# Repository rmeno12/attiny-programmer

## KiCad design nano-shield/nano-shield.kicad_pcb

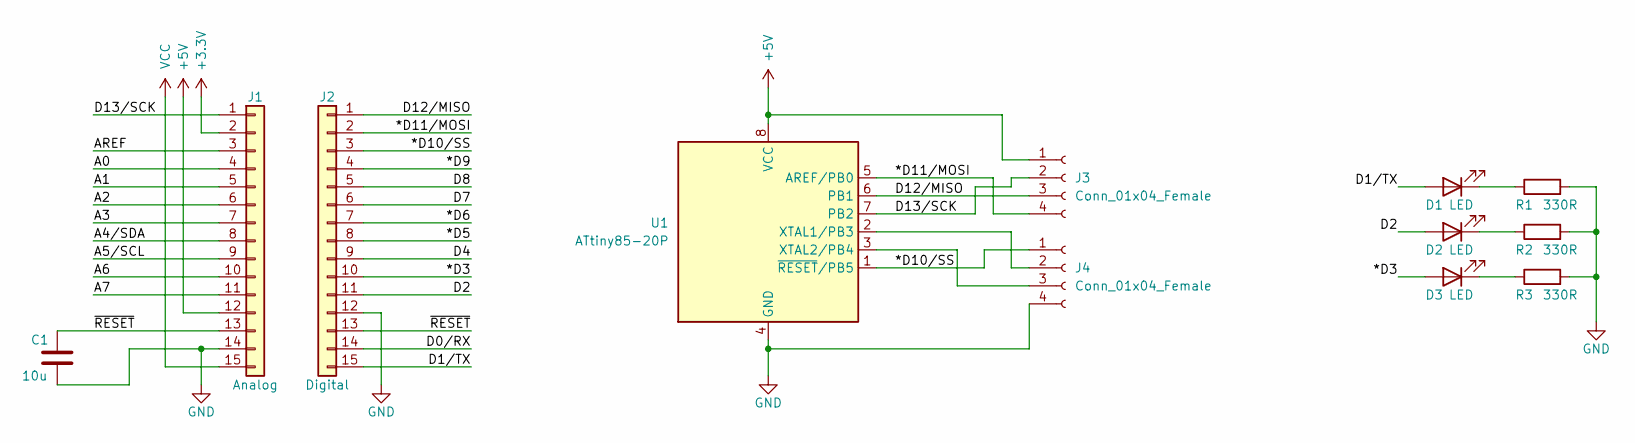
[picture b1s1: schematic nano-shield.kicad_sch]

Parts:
C1: 10u; C_0603_1608Metric
D1, D2, D3: LED; LED_0603_1608Metric
J1: Analog; PinSocket_1x15_P2.54mm_Vertical
J2: Digital; PinSocket_1x15_P2.54mm_Vertical
J3, J4: Conn_01x04_Female; PinSocket_1x04_P2.54mm_Vertical
R1, R2, R3: 330R; R_0603_1608Metric
U1: ATtiny85-20P; DIP-8_W7.62mm_Socket

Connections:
+3V3: J1.2
+5V: J1.12, J3.1, U1.8 (VCC)
/*D3: D3.2 (A), J2.10
/*D5: J2.8
/*D6: J2.7
/*D9: J2.4
/*D10/SS: J2.3, J4.1, U1.1 (~RESET/PB5)
/*D11/MOSI: J2.2, J3.4, U1.5 (AREF/PB0)
/A0: J1.4
/A1: J1.5
/A2: J1.6
/A3: J1.7
/A4/SDA: J1.8
/A5/SCL: J1.9
/A6: J1.10
/A7: J1.11
/AREF: J1.3
/D0/RX: J2.14
/D1/TX: D1.2 (A), J2.15
/D2: D2.2 (A), J2.11
/D4: J2.9
/D7: J2.6
/D8: J2.5
/D12/MISO: J2.1, J3.3, U1.6 (PB1)
/D13/SCK: J1.1, J3.2, U1.7 (PB2)
/~RESET: C1.1, J1.13, J2.13
GND: C1.2, J1.14, J2.12, J4.4, R1.2, R2.2, R3.2, U1.4 (GND)
unnamed: D1.1 (K), R1.1
unnamed: D2.1 (K), R2.1
unnamed: D3.1 (K), R3.1
unnamed: J4.2, U1.2 (XTAL1/PB3)
unnamed: J4.3, U1.3 (XTAL2/PB4)
VCC: J1.15

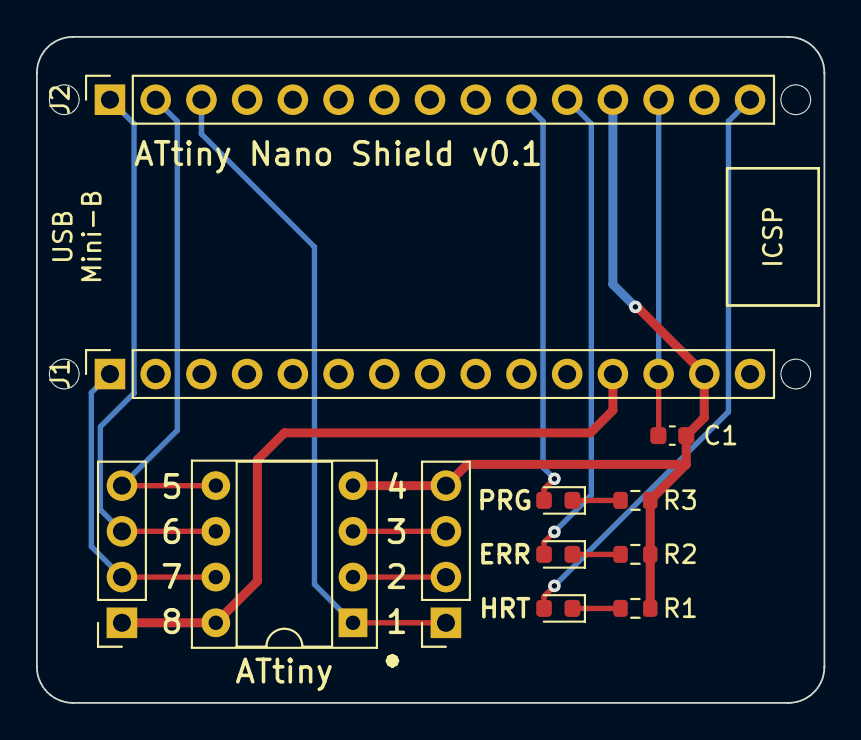
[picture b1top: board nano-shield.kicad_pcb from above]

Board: 2 copper layers, 43.8 x 37.0 mm, 16 parts (0 on the bottom side), 15 nets.

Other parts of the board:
MH1, MH2, MH3, MH4: MountingHole_65mil

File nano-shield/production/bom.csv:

Designator,Footprint,Quantity,Value,LCSC Part #
C1,C_0603_1608Metric,1,10u,
"D1, D2, D3",LED_0603_1608Metric,3,LED,
J1,PinSocket_1x15_P2.54mm_Vertical,1,Analog,
J2,PinSocket_1x15_P2.54mm_Vertical,1,Digital,
"J3, J4",PinSocket_1x04_P2.54mm_Vertical,2,Conn_01x04_Female,
"R1, R2, R3",R_0603_1608Metric,3,330R,
U1,DIP-8_W7.62mm_Socket,1,ATtiny85-20P,

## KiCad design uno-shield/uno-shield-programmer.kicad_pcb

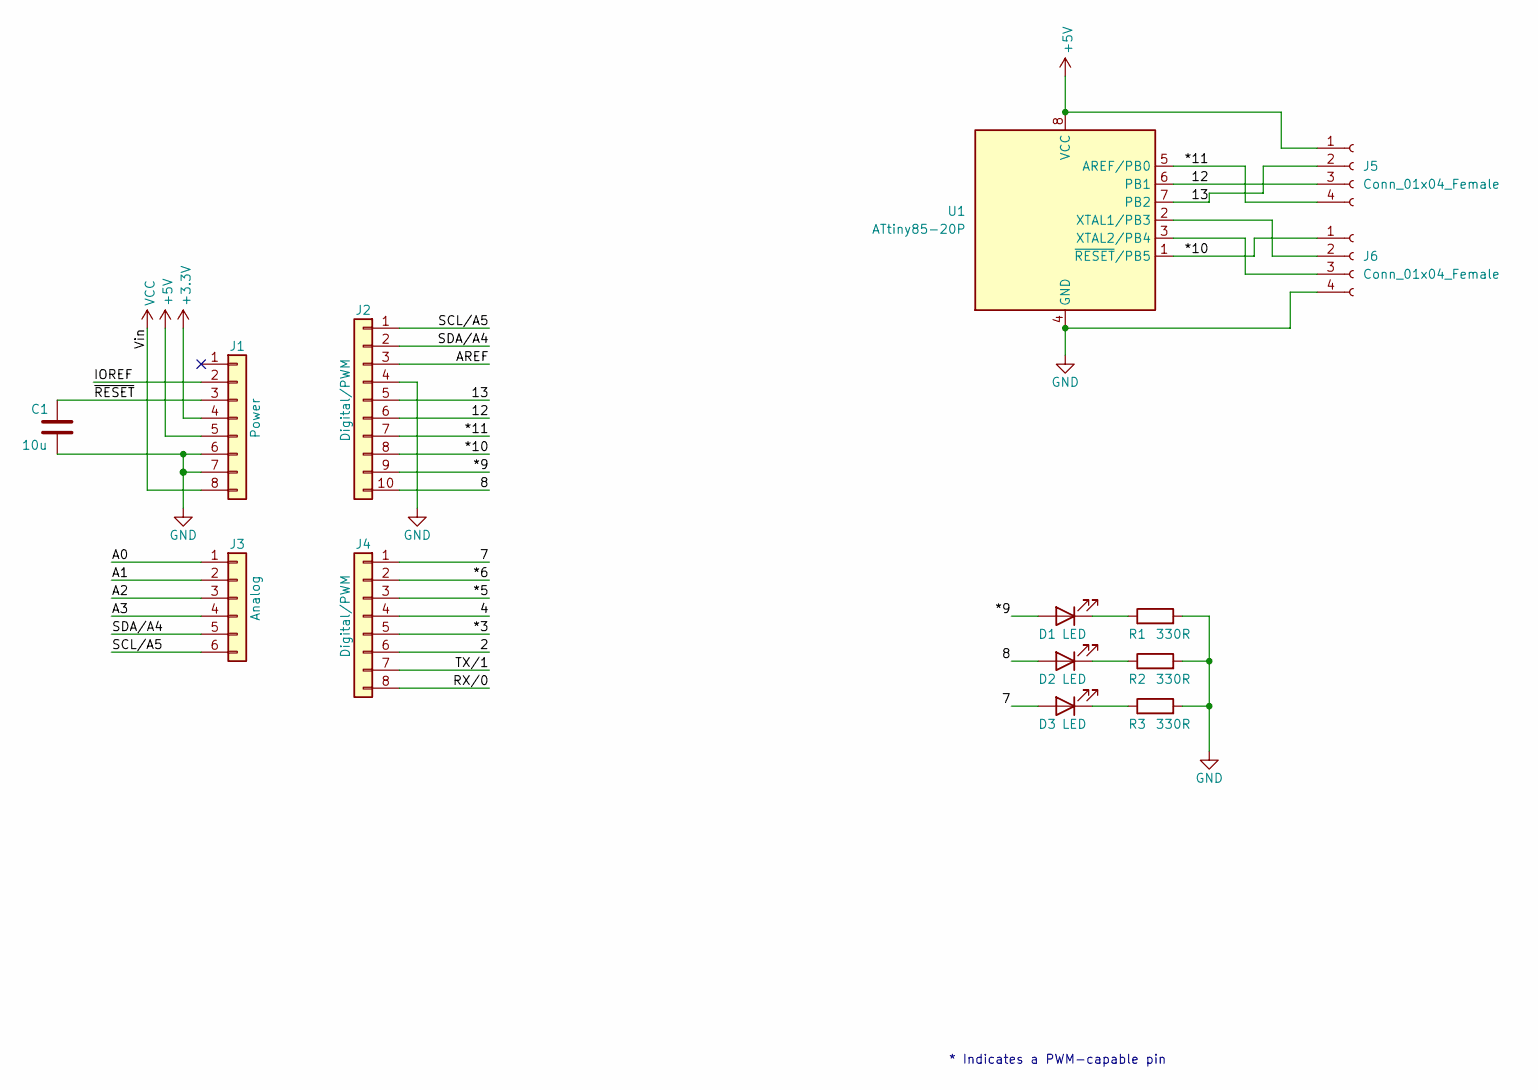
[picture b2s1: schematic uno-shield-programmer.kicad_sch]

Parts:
C1: 10u; C_0603_1608Metric
D1, D2, D3: LED; LED_0603_1608Metric
J1: Power; PinSocket_1x08_P2.54mm_Vertical
J2: Digital/PWM; PinSocket_1x10_P2.54mm_Vertical
J3: Analog; PinSocket_1x06_P2.54mm_Vertical
J4: Digital/PWM; PinSocket_1x08_P2.54mm_Vertical
J5, J6: Conn_01x04_Female; PinSocket_1x04_P2.54mm_Vertical
R1, R2, R3: 330R; R_0603_1608Metric
U1: ATtiny85-20P; DIP-8_W7.62mm_Socket

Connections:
+3V3: J1.4
+5V: J1.5, J5.1, U1.8 (VCC)
/2: J4.6
/4: J4.4
/7: D3.2 (A), J4.1
/8: D2.2 (A), J2.10
/12: J2.6, J5.3, U1.6 (PB1)
/13: J2.5, J5.2, U1.7 (PB2)
/*3: J4.5
/*5: J4.3
/*6: J4.2
/*9: D1.2 (A), J2.9
/*10: J2.8, J6.1, U1.1 (~RESET/PB5)
/*11: J2.7, J5.4, U1.5 (AREF/PB0)
/A0: J3.1
/A1: J3.2
/A2: J3.3
/A3: J3.4
/AREF: J2.3
/IOREF: J1.2
/RX/0: J4.8
/SCL/A5: J2.1, J3.6
/SDA/A4: J2.2, J3.5
/TX/1: J4.7
/~RESET: C1.1, J1.3
GND: C1.2, J1.6, J1.7, J2.4, J6.4, R1.2, R2.2, R3.2, U1.4 (GND)
unnamed: D1.1 (K), R1.1
unnamed: D2.1 (K), R2.1
unnamed: D3.1 (K), R3.1
unnamed: J6.2, U1.2 (XTAL1/PB3)
unnamed: J6.3, U1.3 (XTAL2/PB4)
VCC: J1.8

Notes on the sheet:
* Indicates a PWM-capable pin

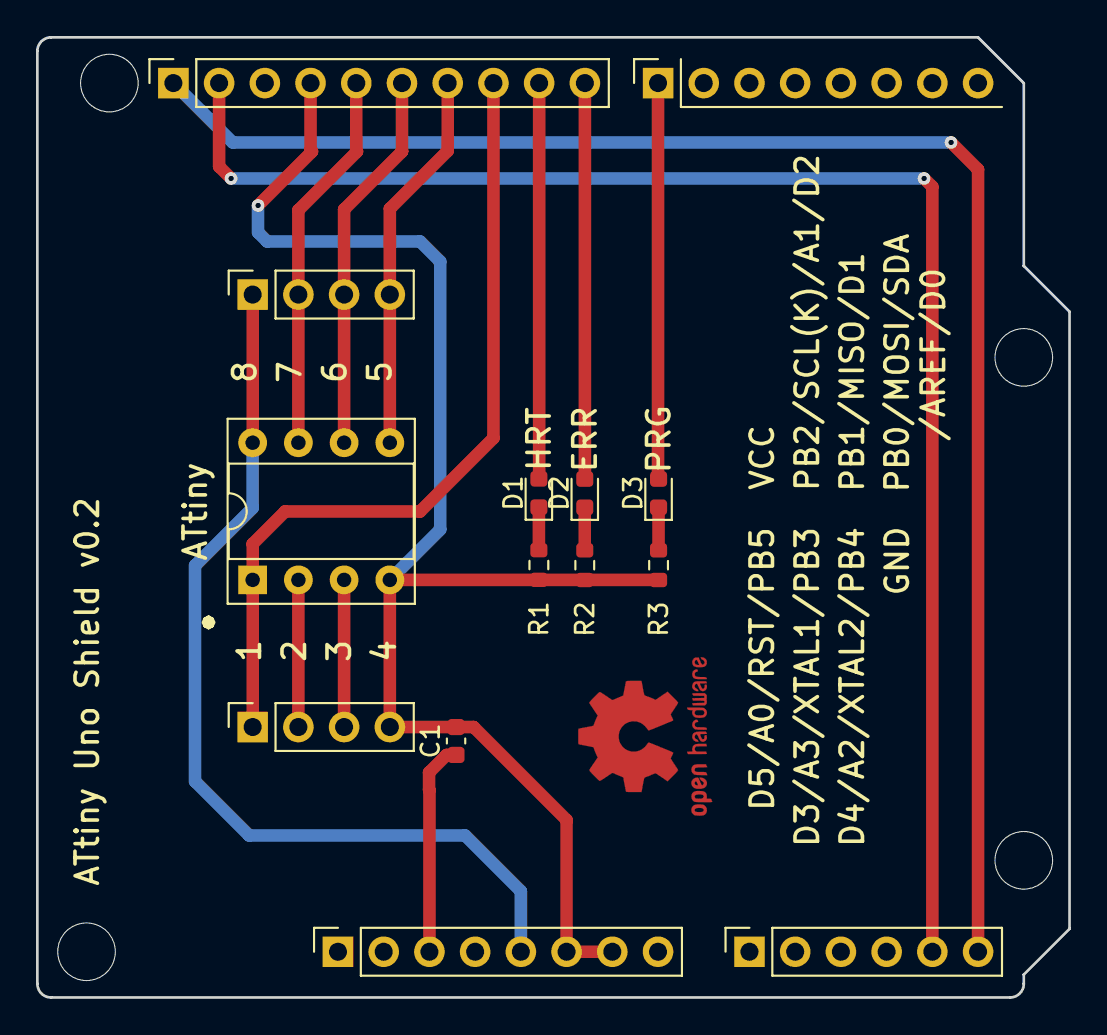
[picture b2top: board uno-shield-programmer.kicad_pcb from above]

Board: 2 copper layers, 57.3 x 53.3 mm, 18 parts (0 on the bottom side), 17 nets.

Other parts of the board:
MH1, MH2, MH3, MH4: MountingHole_3.2mm

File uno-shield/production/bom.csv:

Designator,Footprint,Quantity,Value,LCSC Part #
C1,C_0603_1608Metric,1,10u,
"D1, D2, D3",LED_0603_1608Metric,3,LED,
J1,PinSocket_1x08_P2.54mm_Vertical,1,Power,
J2,PinSocket_1x10_P2.54mm_Vertical,1,Digital/PWM,
J3,PinSocket_1x06_P2.54mm_Vertical,1,Analog,
J4,PinSocket_1x08_P2.54mm_Vertical,1,Digital/PWM,
"J5, J6",PinSocket_1x04_P2.54mm_Vertical,2,Conn_01x04_Female,
"R1, R2, R3",R_0603_1608Metric,3,330R,
U1,DIP-8_W7.62mm_Socket,1,ATtiny85-20P,

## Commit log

2022-10-29 initial uno shield
2022-10-29 move stuff to uno-specific project, add 10uF cap, change to 0603 instead of 0402
2022-10-29 uno v0.2
2022-10-29 nano shield v0.1
